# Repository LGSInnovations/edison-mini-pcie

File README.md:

Edison mini PCI-express Block
=============================

This PCB give the Intel Edison the ability to connect to a mini PCI-express card, such as a wifi/cellular network cards, SD/SDHC storage cards, or any other peripheral that connects to the Edison through USB.

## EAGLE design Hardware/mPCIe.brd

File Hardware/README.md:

mPCIe Edison Block Hardware Guide
=================================

The mPCIe has a downstream USB hub connected to the Edison's OTG port. This allows an additional downstream USB for the user, and one for the mini PCI-express connector. This block also has a SIM card spot, circuitry to detect battery usage on the Edison, and a USB-to-UART port for Linux debugging.

This board is intended to be a termination block, i.e., there is no bottom Hirose connector.

## Components ##

| Component 		| Description										| Resources                                                                                                  |
| :-----------------|:--------------------------------------------------| -----------------------------------------------------------------------------------------------------------|
| USB2512b 			| USB 2.0 High-speed hub w/ 2 downstream ports 		| [Datasheet](http://ww1.microchip.com/downloads/en/DeviceDoc/00001692.pdf)
| FT231XS-U 		| USB-to-UART FTDI chip								| [Datasheet](http://www.ftdichip.com/Support/Documents/DataSheets/ICs/DS_FT231X.pdf)
| TPS62065 			| 2A 3MHz DC-DC step-down converter, set to 4v		| [Datasheet](http://www.ti.com/lit/ds/symlink/tps62065.pdf)
| BA33DD0WHFP 		| 3.3v/2A LDO 										| [Datasheet](http://rohmfs.rohm.com/en/products/databook/datasheet/ic/power/linear_regulator/baxxdd0-e.pdf)
| BA15BC0FP 		| 1.5v/1A LDO 										| [Datasheet](http://www.mouser.com/ds/2/348/baxxbc0fp-e-209385.pdf)
| MAX4995AAUT 		| USB Port Power current limiter IC, set to ~480mA  | [Datasheet](http://datasheets.maximintegrated.com/en/ds/MAX4995A-MAX4995C.pdf)
| BSS138 			| MOSFET to control `DCIN` input to Edison			| [Datasheet](https://www.fairchildsemi.com/datasheets/BS/BSS138.pdf)

## Power Requirements ##

To power the mPCIe block and the Edison, at least a 5v/2A connection is required to the USB-to-UART console port. This 2A is used by the following major components:

| Component                | Current Draw                    |
| :----------------------- |:--------------------------------|
| The Intel Edison         | ~250mA (3.3-4.5v @ <1W)         |
| The USB Hub (USB2512b)   | 155mA					         |
| mini PCI-express device  | typically 500-700mA w/ 2A spikes|
| downstream usb device    | 480mA maximum (due to MAX4995)  |

#### Powering the Block ####

Power comes into the block through the USB MicroB (JP1) console port. This voltage is then stepped down using a 5v to 4v/2A 3MHz converter (TPS62065). This feeds `VSYS`, which powers the Edison. The Edison converts this `VSYS` to 3.3v on pins 8 and 10; each can source 100mA, giving a theoritical 200mA given that these pins are tied together. Edison also converts to 1.8v on pin 12, also sourcing 100mA.

`VSYS` also feeds a 3.3v/2A LDO and an optional 1.5v/1A LDO. These LDOs power the mini PCI-express card.

The downstream USB is powered directly by the USB-to-UART's `USB_VBUS` pin. It is current limited by the MAX4995AAUT IC to ~480mA.

Consider using a [y-cable](http://www.amazon.com/StarTech-3-Feet-Cable-External-Drive/dp/B0047AALS0) to provide power and the console when using a computer.

#### Current Spikes ####

Because many devices that would be insterted into the mini PCI-express slot can experience up to 2A transient current spikes, a tantalum 470uF capacitor is placed near the 3.3v power supply.

---------------------------------------

## Resources ##

| Item                     | Description                     | Resource
| :----------------------- |:--------------------------------|:--------------------------
| SparkFun Base Block      | Power and FTDI example          | [Schematic](https://cdn.sparkfun.com/datasheets/Dev/Edison/Base_Block.pdf)
| USBMA Wireless Adapter   | mPCIe, power, SIM, example		 | [Schematic](http://www.hwtools.net/PDF/USBMA_ver1.2f_schematic.pdf)
| USB2514b Dev Board       | Example of USB2512b IC          | [Schematic](http://ww1.microchip.com/downloads/en/DeviceDoc/evb2514qfn48.pdf)
| USB2514b Dev Board       | Parts List                      | [BOM](http://ww1.microchip.com/downloads/en/DeviceDoc/evb2514qfn48bom.pdf)

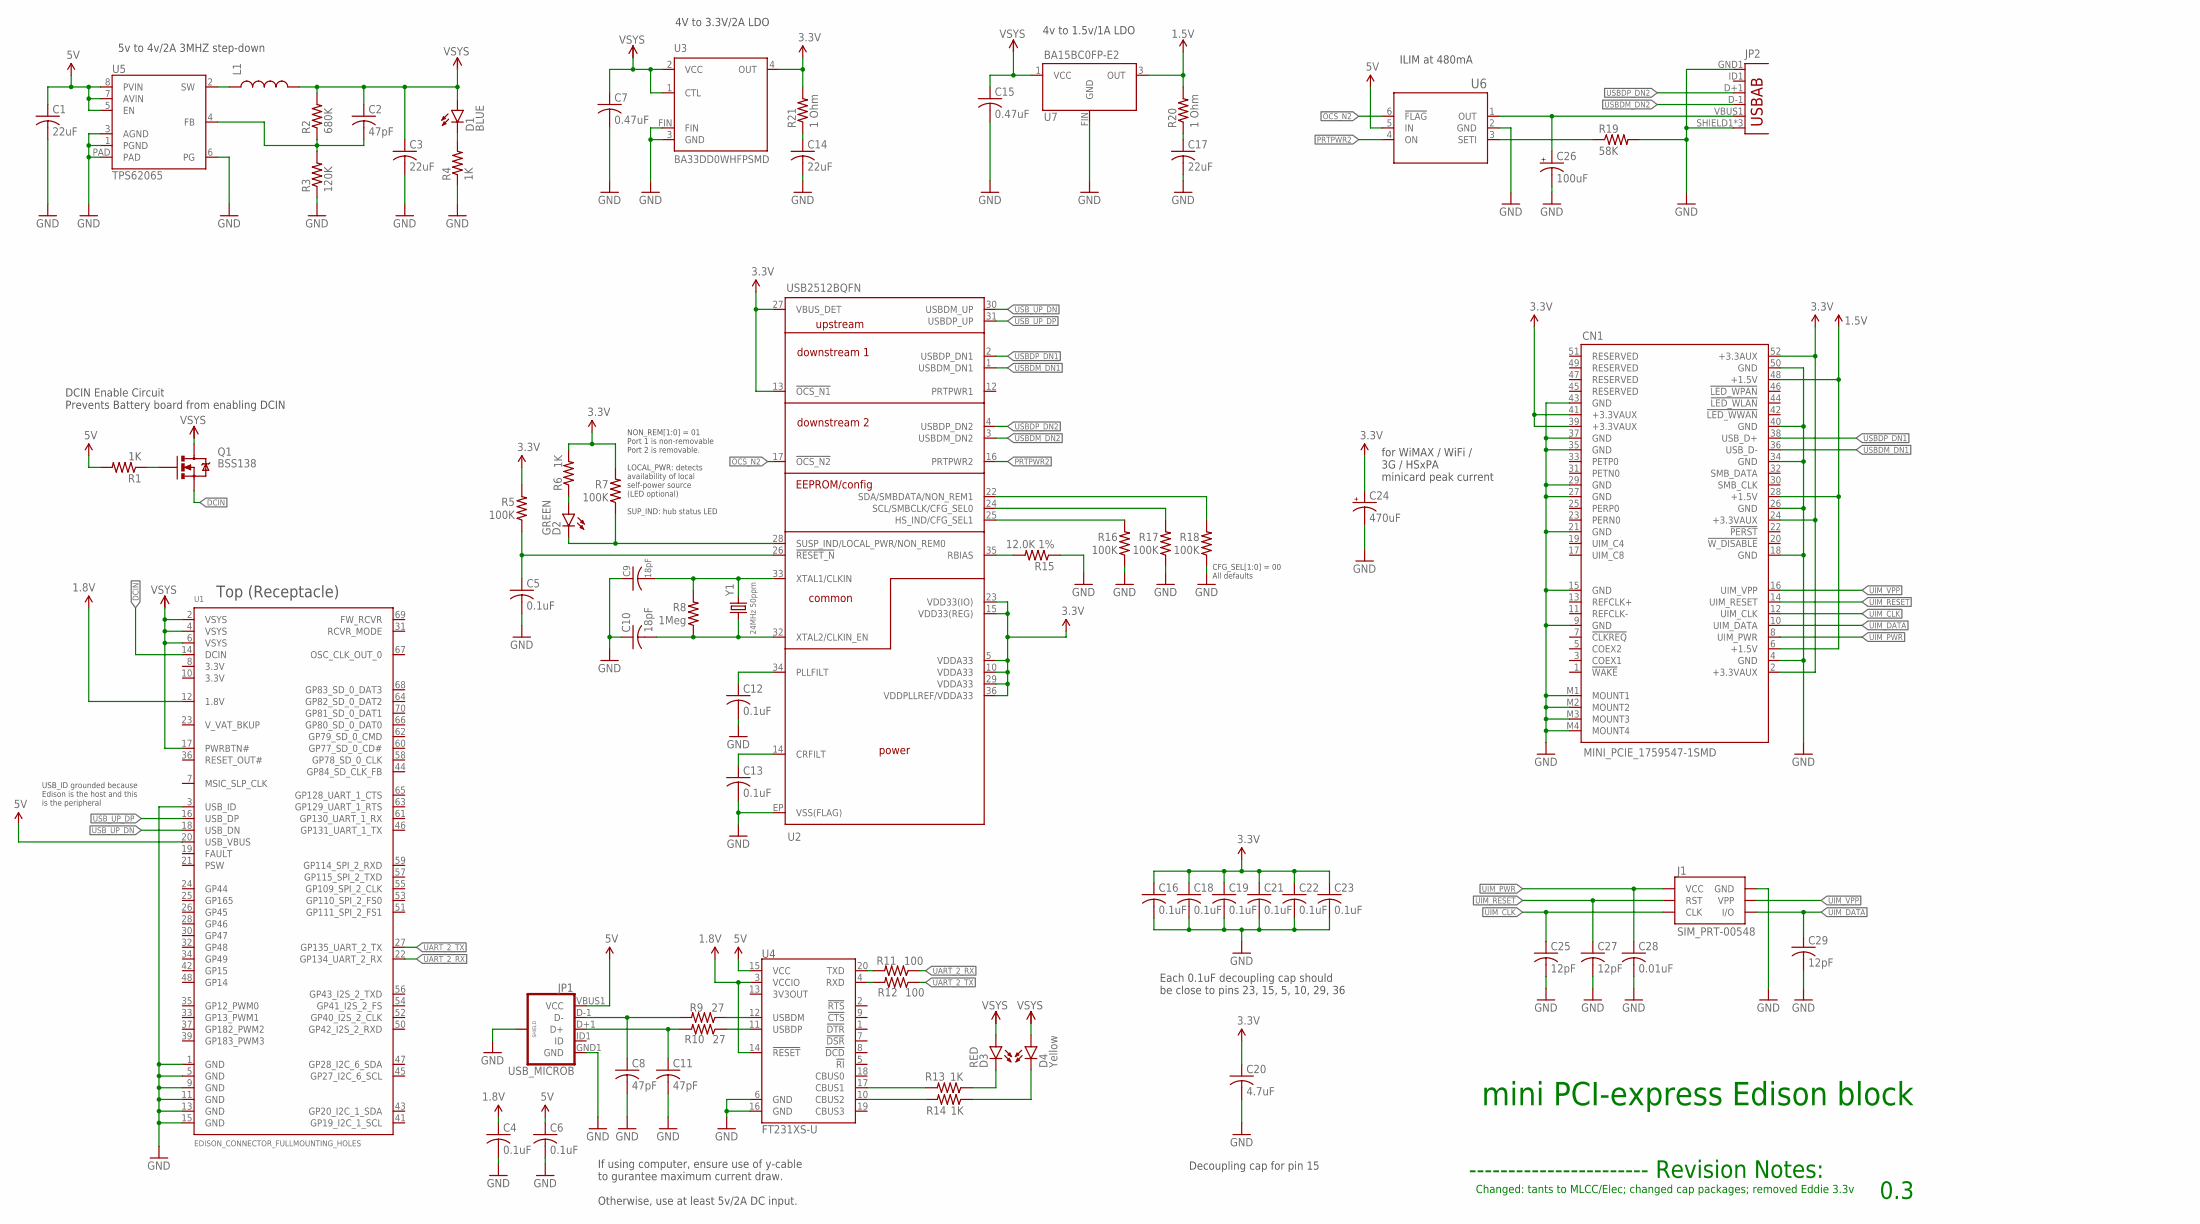
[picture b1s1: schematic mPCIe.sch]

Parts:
C1, C3, C14, C17: 22uF; C0603K
C2, C8, C11: 47pF; C0402K
C4, C5, C6, C12, C13, C16, C18, C19, C21, C22, C23: 0.1uF; C0402K
C7, C15: 0.47uF; C0402K
C9, C10: 18pF; C0402K
C20: 4.7uF; C0603K
C24: 470uF; PANASONIC_E
C25, C27, C29: 12pF; C0402K
C26: 100uF; PANASONIC_E
C28: 0.01uF; C0402K
CN1: MINI_PCIE_1759547-1SMD; MINI_PCIE_1759547-1
D1: BLUE; LED-0603
D2: GREEN; LED-0603
D3: RED; LED-0603
D4: Yellow; LED-0603
J1: SIM_PRT-00548; SIMHOLDER
JP1: USB_MICROB; USB-B-MICRO-SMD_V03
JP2: USB-ABCONN-11794; USB-AB-MICRO-SMD_V03
L1: INDUCTOR; INDUCTOR-SRP4020
Q1: BSS138; SOT23-3
R1, R4, R6, R13, R14: 1K; R0402
R2: 680K; R0402
R3: 120K; R0402
R5, R7, R16, R17, R18: 100K; R0402
R8: 1Meg; R0402
R9, R10: 27; R0402
R11, R12: 100; R0402
R15: 12.0K 1%; R0402
R19: 58K; R0402
R20, R21: 1 Ohm; R0402
U1: EDISON_CONNECTOR_FULLMOUNTING_HOLES; EDISON_DAUGHTER
U2: USB2512BQFN; QFN-36
U3: BA33DD0WHFPSMD; HRP5
U4: FT231XS-U; SSOP20_L
U5: TPS62065; WSON-8-PAD
U6: MAX4995AAUT+; 21-0058I
U7: BA15BC0FP-E2; TO252-3
Y1: 24MHz 50ppm; CRYSTAL-SMD-5X3

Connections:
1.5V: CN1.6 (+1.5V), CN1.28 (+1.5V), CN1.48 (+1.5V)
1.8V: C4.1, U1.12 (1.8V), U4.3 (VCCIO), U4.14 (!RESET)
3.3V: C16.1, C18.1, C19.1, C20.1, C21.1, C22.1, C23.1, C24.+, CN1.2 (+3.3VAUX), CN1.24 (+3.3VAUX), CN1.39 (+3.3VAUX), CN1.41 (+3.3VAUX), CN1.52 (+3.3AUX), R5.2, R6.2, R7.2, R21.2, U2.5 (VDDA33), U2.10 (VDDA33), U2.13 (!OCS_N1), U2.15 (VDD33(REG)), U2.23 (VDD33(IO)), U2.27 (VBUS_DET), U2.29 (VDDA33), U2.36 (VDDPLLREF/VDDA33), U3.4 (OUT)
5V: C1.1, C6.1, JP1.VBUS1 (VCC), R1.2, U1.20 (USB_VBUS), U4.15 (VCC), U5.5 (EN), U5.7 (AVIN), U5.8 (PVIN), U6.5 (IN)
DCIN: Q1.2 (S), U1.14 (DCIN)
GND: C1.2, C3.2, C4.2, C5.2, C6.2, C7.2, C8.2, C9.1, C10.1, C11.2, C12.2, C13.2, C14.2, C15.2, C16.2, C17.2, C18.2, C19.2, C20.2, C21.2, C22.2, C23.2, C24.-, C25.2, C26.-, C27.2, C28.2, C29.2, CN1.4 (GND), CN1.9 (GND), CN1.15 (GND), CN1.18 (GND), CN1.21 (GND), CN1.26 (GND), CN1.27 (GND), CN1.29 (GND), CN1.34 (GND), CN1.35 (GND), CN1.37 (GND), CN1.40 (GND), CN1.43 (GND), CN1.50 (GND), CN1.M1 (MOUNT1), CN1.M2 (MOUNT2), CN1.M3 (MOUNT3), CN1.M4 (MOUNT4), J1.C5 (GND), JP1.GND1 (GND), JP1.SHIELD1 (SHIELD), JP1.SHIELD2 (SHIELD), JP1.SHIELD3 (SHIELD), JP2.GND1 (GND), JP2.SHIELD1 (SHIELD), JP2.SHIELD2 (SHIELD), JP2.SHIELD3 (SHIELD), R3.1, R4.1, R15.1, R16.1, R17.1, R18.1, R19.2, U1.1 (GND), U1.3 (USB_ID), U1.5 (GND), U1.9 (GND), U1.11 (GND), U1.13 (GND), U1.15 (GND), U2.EP (VSS(FLAG)), U3.3 (GND), U3.FIN, U4.6 (GND), U4.16 (GND), U5.1 (PGND), U5.3 (AGND), U5.6 (PG), U5.PAD, U6.2 (GND), U7.FIN (GND)
unnamed: C13.1, U2.14 (CRFILT)
unnamed: C9.2, R8.2, U2.33 (XTAL1/CLKIN), Y1.3 (2)
unnamed: C12.1, U2.34 (PLLFILT)
unnamed: C10.2, R8.1, U2.32 (XTAL2/CLKIN_EN), Y1.1
unnamed: R15.2, U2.35 (RBIAS)
unnamed: C5.1, R5.1, U2.26 (!RESET_N)
unnamed: D2.C, R7.1, U2.28 (SUSP_IND/LOCAL_PWR/NON_REM0)
unnamed: R18.2, U2.22 (SDA/SMBDATA/NON_REM1)
unnamed: C26.+, JP2.VBUS1 (VBUS), U6.1 (OUT)
unnamed: R16.2, U2.25 (HS_IND/CFG_SEL1)
unnamed: R9.1, U4.12 (USBDM)
unnamed: R17.2, U2.24 (SCL/SMBCLK/CFG_SEL0)
unnamed: R10.1, U4.11 (USBDP)
unnamed: C8.1, JP1.D-1 (D-), R9.2
unnamed: C11.1, JP1.D+1 (D+), R10.2
unnamed: C17.1, R20.1
unnamed: R11.2, U4.20 (TXD)
unnamed: R12.2, U4.4 (RXD)
unnamed: R14.2, U4.10 (CBUS2)
unnamed: R13.2, U4.17 (CBUS1)
unnamed: C14.1, R21.1
unnamed: D3.C, R13.1
unnamed: D4.C, R14.1
unnamed: Q1.1 (G), R1.1
unnamed: L1.P$1 (1), U5.2 (SW)
unnamed: C2.2, R2.1, R3.2, U5.4 (FB)
unnamed: R19.1, U6.3 (SETI)
unnamed: D2.A, R6.1
unnamed: D1.C, R4.2
OCS_N2: U2.17 (!OCS_N2), U6.6 (!FLAG)
P$1: R20.2, U7.3 (OUT)
PRTPWR2: U2.16 (PRTPWR2), U6.4 (ON)
UART_2_RX: R11.1, U1.22 (GP134_UART_2_RX)
UART_2_TX: R12.1, U1.27 (GP135_UART_2_TX)
UIM_CLK: C25.1, CN1.12 (UIM_CLK), J1.C3 (CLK)
UIM_DATA: C29.1, CN1.10 (UIM_DATA), J1.C7 (I/O)
UIM_PWR: C28.1, CN1.8 (UIM_PWR), J1.C1 (VCC)
UIM_RESET: C27.1, CN1.14 (UIM_RESET), J1.C2 (RST)
UIM_VPP: CN1.16 (UIM_VPP), J1.C6 (VPP)
USBDM_DN1: CN1.36 (USB_D-), U2.1 (USBDM_DN1)
USBDM_DN2: JP2.D-1 (D-), U2.3 (USBDM_DN2)
USBDP_DN1: CN1.38 (USB_D+), U2.2 (USBDP_DN1)
USBDP_DN2: JP2.D+1 (D+), U2.4 (USBDP_DN2)
USB_UP_DN: U1.18 (USB_DN), U2.30 (USBDM_UP)
USB_UP_DP: U1.16 (USB_DP), U2.31 (USBDP_UP)
VSYS: C2.1, C3.1, C7.1, C15.1, D1.A, D3.A, D4.A, L1.P$2 (2), Q1.3 (D), R2.2, U1.2 (VSYS), U1.4 (VSYS), U1.6 (VSYS), U1.17 (PWRBTN#), U3.1 (CTL), U3.2 (VCC), U7.1 (VCC)

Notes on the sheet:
Top (Receptacle)
NON_REM[1:0] = 01 Port 1 is non-removable Port 2 is removable. LOCAL_PWR: detects availability of local self-power source (LED optional) SUP_IND: hub status LED
CFG_SEL[1:0] = 00 All defaults
USB_ID grounded because Edison is the host and this is the peripheral
4V to 3.3V/2A LDO
DCIN Enable Circuit Prevents Battery board from enabling DCIN
for WiMAX / WiFi / 3G / HSxPA minicard peak current
If using computer, ensure use of y-cable to gurantee maximum current draw. Otherwise, use at least 5v/2A DC input.
5v to 4v/2A 3MHZ step-down
ILIM at 480mA
4v to 1.5v/1A LDO
mini PCI-express Edison block
0.3
----------------------- Revision Notes:
Changed: tants to MLCC/Elec; changed cap packages; removed Eddie 3.3v
JP2
Each 0.1uF decoupling cap should be close to pins 23, 15, 5, 10, 29, 36
Decoupling cap for pin 15

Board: 4 copper layers, 68 parts (6 on the bottom side), 52 nets, no tracks yet.

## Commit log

2015-07-15 added Hardware folder with HW guide readme
2015-07-15 added schematic v0.1
2015-07-15 added datasheet links and resources
2015-07-17 add revision 0.2 of the schematic; added initial board layout; renumbered components; removed solder jumpers; schematic style considerations
2015-07-21 moved all components onto layout; grouped by major function
2015-07-31 v0.3 of schematic: connected all the 3.3v nets to PSUs and not Edison; removed tantalum caps; replaced LDO Vout caps with MLCCs and series ESRs; laid out board and ready to route

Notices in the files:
parts and their libraries:
SparkFun-Capacitors: Licensing: Creative Commons ShareAlike 4.0 International - https://creativecommons.org/licenses/by-sa/4.0
